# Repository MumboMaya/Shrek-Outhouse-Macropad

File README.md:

# Shrek--Outhouse-Macropad
The  Shrek's Outhouse Macropad is a 2x3 Macropad that looks like Shrek’s outhouse. It was made to make everyday tasks, such as switching tabs, easier. It is also designed to be used as a device that can be set to do anything, for example, starting a recording in OBS.

# Features
- 6 programmable keys
- USB-C support
- Modelled after Shrek’s outhouse with its features, such as the crescent moon 

# CAD Model
Everything fits together using X4 M3x18 Bolts and x4 M3 nuts

My CAD Model has 3 different 3D printable parts. After putting together the bottom and middle part you pust then insert the PCB and then wire all your components. Once that is finished, you can place the top cover.  This Macropad holds 6 differenrt programable keys. 

Onshape project: https://cad.onshape.com/documents/106fde0273fca8a43f39e24d/w/18bff7a09fb1d6f77b12e438/e/b6e0fe9afac343b420846645?renderMode=0&uiState=69c4f5f4dcf056a8a53934ab

# PCB
Here is my PCB, it was made using Kicad!

### Schematic:

### PCB:

# Firmware Overview
QMK is used to generate the firmware and VIA is used to remap the keys without re-flashing the macropad. One the macropad is flashed with the VIA-enabled firmware, the macropad keymap can be changed using https://www.usevia.app/ in a CHROMIUM BASED browser (it will not work in non-chromium based browsers due to lack of WebHID support). With this website you can see what browsers are supported: https://caniuse.com/?search=webhid. The VIA desktop app can also be used.

### Features:

- VIA-enabled dynamic keymaps
- EEPROM-based configuration storage so that keymaps are remembered between powercycles
- Bootmagic support for resetting
- Compatible with VIA web app and VIA desktop app

# BOM
Here is everything you will need to make this macropad!

- X6 DSA Keycaps
- X6 Cherry MX Switches
- X4 M3x18 bolts
- X4 M3 nuts
- X1 Seeduino XIAO RP2040

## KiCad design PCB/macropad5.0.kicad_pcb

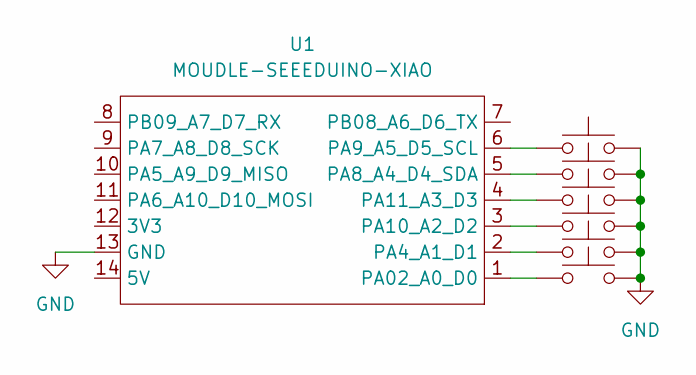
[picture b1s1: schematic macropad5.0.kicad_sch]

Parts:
SW1, SW2, SW3, SW4, SW5, SW6: SW_Push; SW_Cherry_MX_1.00u_PCB
U1: MOUDLE-SEEEDUINO-XIAO; XIAO-Generic-Hybrid-14P-2.54-21X17.8MM

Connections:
GND: SW1.2, SW2.2, SW3.2, SW4.2, SW5.2, SW6.2, U1.13 (GND)
unnamed: SW6.1, U1.1 (PA02_A0_D0)
unnamed: SW4.1, U1.2 (PA4_A1_D1)
unnamed: SW1.1, U1.5 (PA8_A4_D4_SDA)
unnamed: SW5.1, U1.6 (PA9_A5_D5_SCL)
unnamed: SW3.1, U1.3 (PA10_A2_D2)
unnamed: SW2.1, U1.4 (PA11_A3_D3)

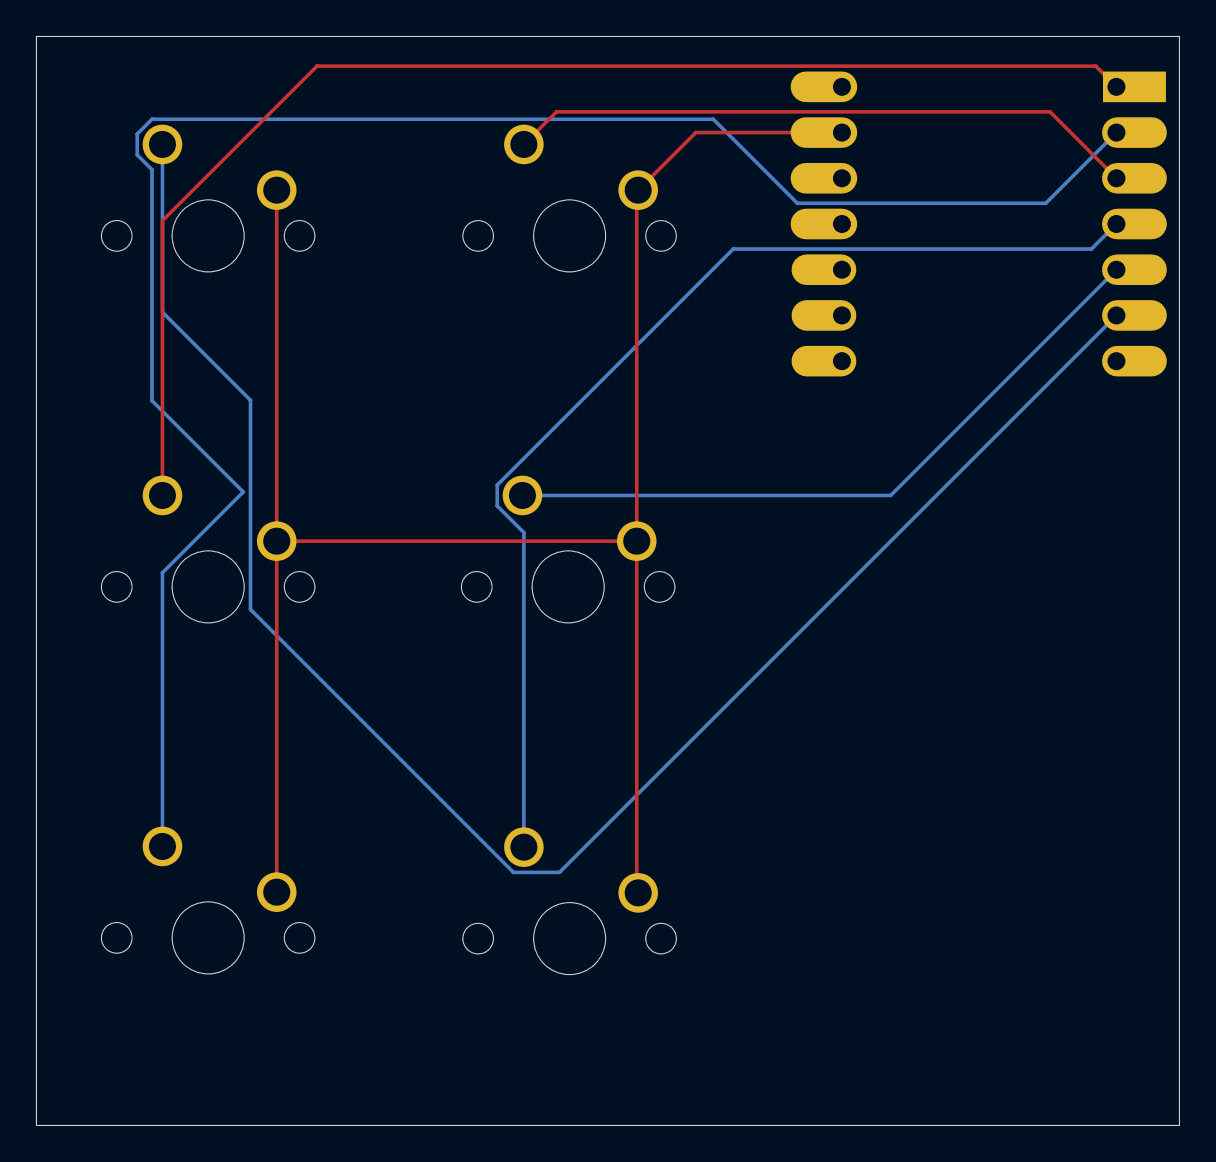
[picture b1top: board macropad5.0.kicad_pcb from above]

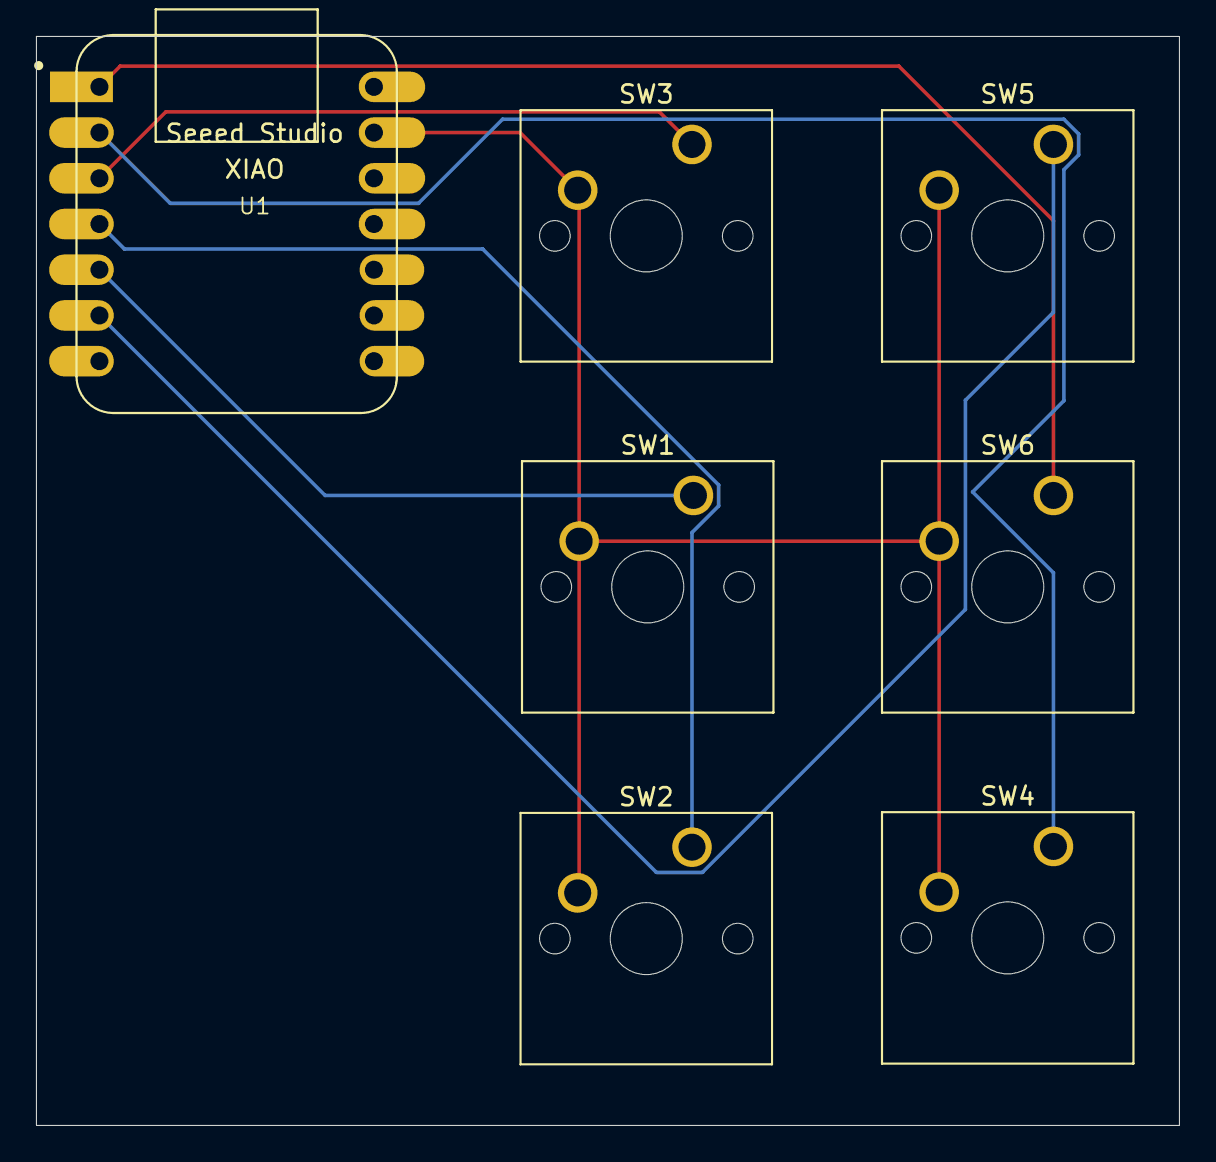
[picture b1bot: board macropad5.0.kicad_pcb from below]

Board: 2 copper layers, 63.5 x 60.5 mm, 7 parts (7 on the bottom side), 7 nets.

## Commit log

2026-03-09 Create CAD
2026-03-16 Create images
2026-03-16 Rename CAD File.jpeg to CAD-File.jpeg
